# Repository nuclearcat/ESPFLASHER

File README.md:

# ESPFLASHER
Inexpensive ESP32/ESP8266 programmer

This device implements a USB programmer for ESP32/ESP8266 devices with traditional programming pin management (EN/BOOT0) using [RTS DTR bridge][1].

It also differs from traditional USB-UART converters by a powerful LDO, which allows you to easily power the ESP32 / ESP8266 and related peripherals.
Earlier revisions were manufactured by JLCPCB and tested for programming various devices.

**V3 has not been tested on physical hardware (IRL) yet.** It uses [USB-C with USB 2.0 data](docs/usb-c.md), corrects the header labels and board-edge clearance, uses a ceramic-compatible TI regulator, and retains a single power LED beside the programming header. The RX/TX activity LEDs and their drivers have been removed. It has passed the KiCad checks described in [the revision notes](docs/revision-3.md). Gerbers, BOM and CPL are included.

[1]: https://raw.githubusercontent.com/nodemcu/nodemcu-devkit/master/Documents/NODEMCU_DEVKIT_SCH.png "Also called Node-MCU auto-program circuit"

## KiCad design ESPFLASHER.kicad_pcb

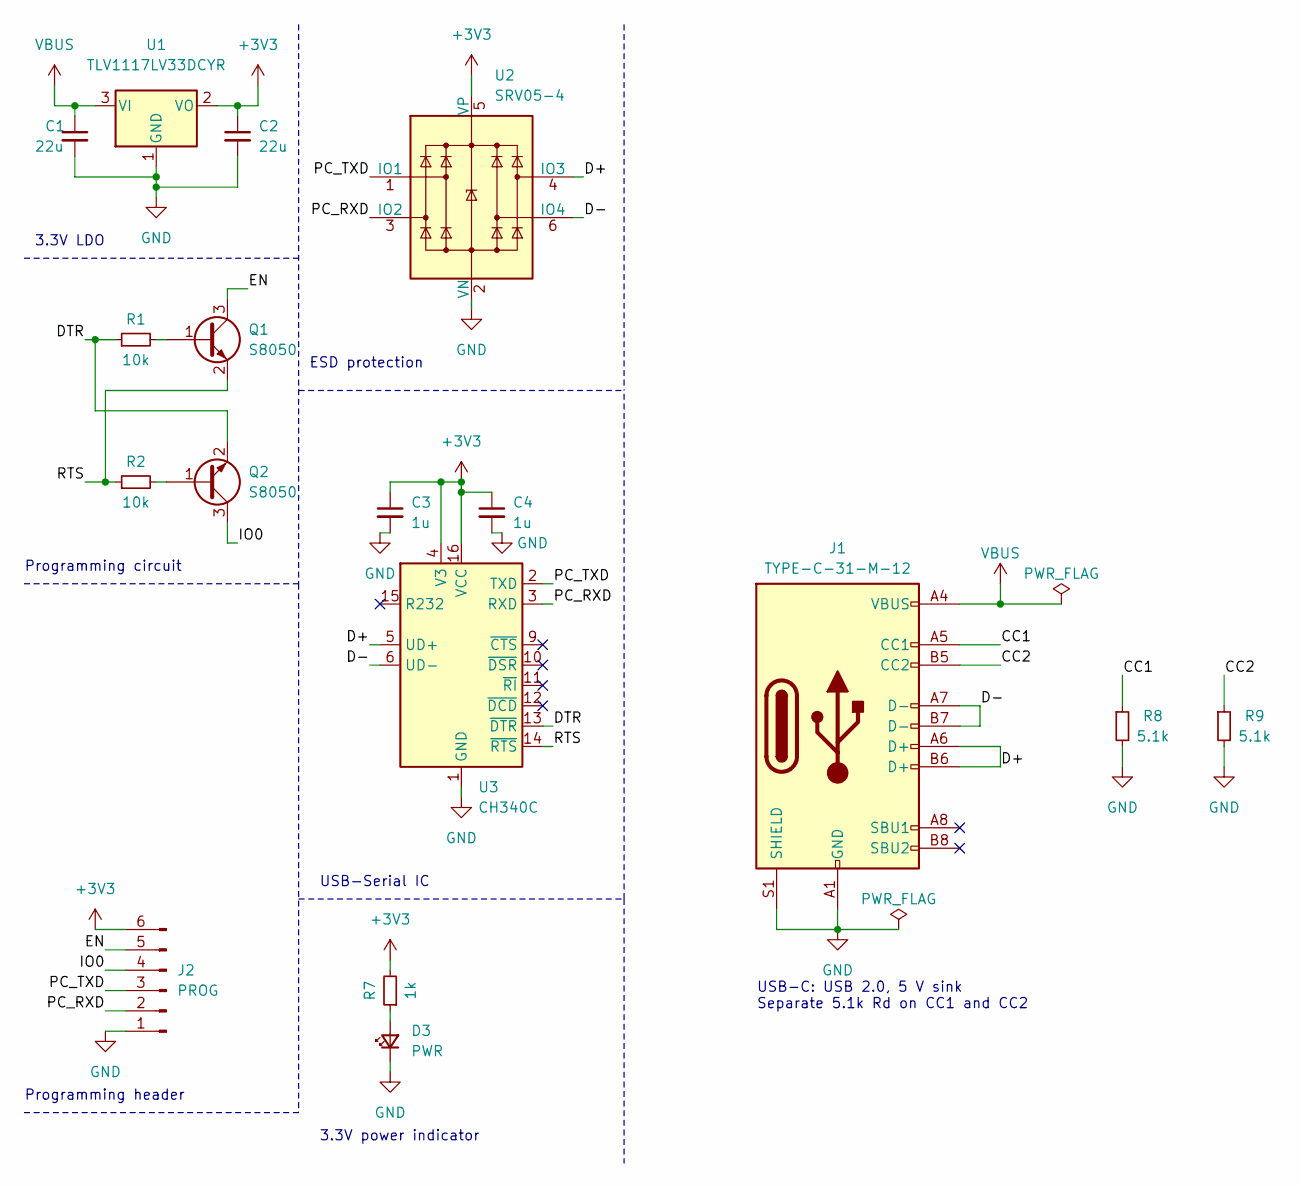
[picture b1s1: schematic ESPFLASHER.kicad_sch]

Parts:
C1, C2: 22u; C_0603_1608Metric; JLCPCB C2762594
C3, C4: 1u; C_0603_1608Metric; JLCPCB C59302
D3: PWR; LED_0603_1608Metric; JLCPCB C2286
J1: TYPE-C-31-M-12; USB_C_Receptacle_HRO_TYPE-C-31-M-12; JLCPCB C165948
J2: PROG; PinHeader_1x06_P2.54mm_Vertical
Q1, Q2: S8050; SOT-23_Handsoldering; JLCPCB C2150
R1, R2: 10k; R_0603_1608Metric; JLCPCB C25804
R7: 1k; R_0603_1608Metric; JLCPCB C21190
R8, R9: 5.1k; R_0603_1608Metric; JLCPCB C23186
U1: TLV1117LV33DCYR; SOT-223-3_TabPin2; JLCPCB C15578
U2: SRV05-4; SOT-23-6; JLCPCB C558418
U3: CH340C; SOIC-16_3.9x9.9mm_P1.27mm; JLCPCB C7464026

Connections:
+3V3: C2.1, C3.1, C4.1, J2.6, R7.2, U1.2 (VO), U2.5 (VP), U3.4 (V3), U3.16 (VCC)
/CC1: J1.A5 (CC1), R8.1
/CC2: J1.B5 (CC2), R9.1
/D+: J1.A6 (D+), J1.B6 (D+), U2.4 (IO3), U3.5 (UD+)
/D-: J1.A7 (D-), J1.B7 (D-), U2.6 (IO4), U3.6 (UD-)
/DTR: Q2.2 (E), R1.1, U3.13 (~DTR)
/EN: J2.5, Q1.3 (C)
/IO0: J2.4, Q2.3 (C)
/PC_RXD: J2.2, U2.3 (IO2), U3.3 (RXD)
/PC_TXD: J2.3, U2.1 (IO1), U3.2 (TXD)
/RTS: Q1.2 (E), R2.1, U3.14 (~RTS)
GND: C1.2, C2.2, C3.2, C4.2, D3.1 (K), J1.A1 (GND), J1.A12 (GND), J1.B1 (GND), J1.B12 (GND), J1.S1 (SHIELD), J2.1, R8.2, R9.2, U1.1 (GND), U2.2 (VN), U3.1 (GND)
unnamed: D3.2 (A), R7.1
unnamed: Q1.1 (B), R1.2
unnamed: Q2.1 (B), R2.2
VBUS: C1.1, J1.A4 (VBUS), J1.A9 (VBUS), J1.B4 (VBUS), J1.B9 (VBUS), U1.3 (VI)

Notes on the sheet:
ESD protection
Programming circuit
Programming header
3.3V power indicator
USB-Serial IC
3.3V LDO
USB-C: USB 2.0, 5 V sink Separate 5.1k Rd on CC1 and CC2

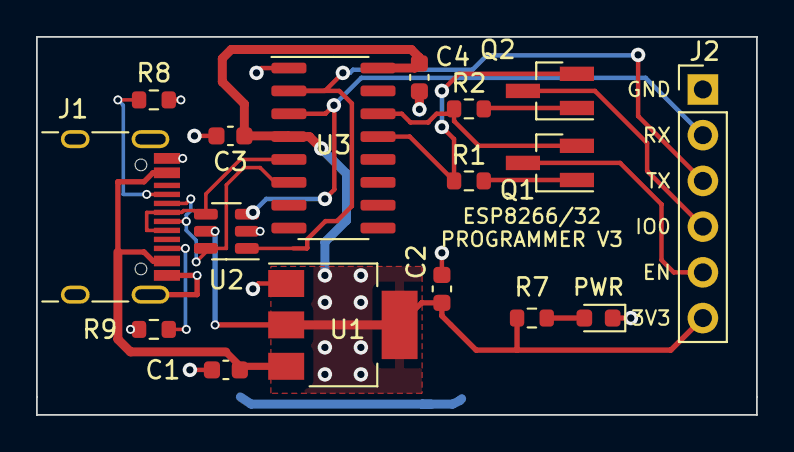
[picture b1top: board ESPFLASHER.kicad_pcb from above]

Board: 2 copper layers, 40.0 x 21.0 mm, 17 parts (0 on the bottom side), 16 nets.

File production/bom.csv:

Designator,Footprint,Quantity,Value,LCSC Part #
"C1, C2",C_0603_1608Metric,2,22u,C2762594
"C3, C4",C_0603_1608Metric,2,1u,C59302
D3,LED_0603_1608Metric,1,PWR,C2286
J1,USB_C_Receptacle_HRO_TYPE-C-31-M-12,1,TYPE-C-31-M-12,C165948
J2,PinHeader_1x06_P2.54mm_Vertical,1,PROG,
"Q1, Q2",SOT-23_Handsoldering,2,S8050,C2150
"R1, R2",R_0603_1608Metric,2,10k,C25804
R7,R_0603_1608Metric,1,1k,C21190
"R8, R9",R_0603_1608Metric,2,5.1k,C23186
U1,SOT-223-3_TabPin2,1,TLV1117LV33DCYR,C15578
U2,SOT-23-6,1,SRV05-4,C558418
U3,SOIC-16_3.9x9.9mm_P1.27mm,1,CH340C,C7464026

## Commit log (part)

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2022-10-18 Add PCB/SCH files
2022-10-18 Add image and pdf
2022-10-18 Change wrong picture
2022-10-18 Add image
2024-05-11 Add changelog
2024-05-11 Remanufacturing, update to latest KiCAD
